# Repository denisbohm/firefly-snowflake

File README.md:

# firefly-snowflake
Firefly Design LLC - Snowflake Christmas Ornament

The snowflake is a Christmas tree ornament with RGB LEDs that light up in various ways.  It has a rechargeable battery (via micro USB port) and it is controllable via BLE via a Swift app.

This repository has all the files to create a snowflake Christmas ornament.  This includes 3D mechanical files to create the plastic parts, Eagle schematics & layout for the PCBA, PCBA firmware, and Swift App source files.

To compile the firmware you need the Nordic nRF5 SDK 12 and Firefly Ice Firmware.  On macOS:

    $ git clone https://github.com/denisbohm/firefly-snowflake.git
    $ cd firefly-snowflake/firmware
    $ git clone https://github.com/denisbohm/firefly-ice-firmware.git
    $ curl https://www.nordicsemi.com/eng/nordic/download_resource/54291/51/54256290 -o nRF5_SDK_12.zip
    $ unzip nRF5_SDK_12.zip -d nRF5_SDK_12

See [Firefly Design LLC](http://fireflydesign.com) for information on the open source Firefly Design repositories.

## Copyright and License
Copyright 2016 Firefly Design LLC / Denis Bohm

This work is licensed under [Creative Commons Attribution 4.0 International](https://licensebuttons.net/l/by/4.0/88x31.png).

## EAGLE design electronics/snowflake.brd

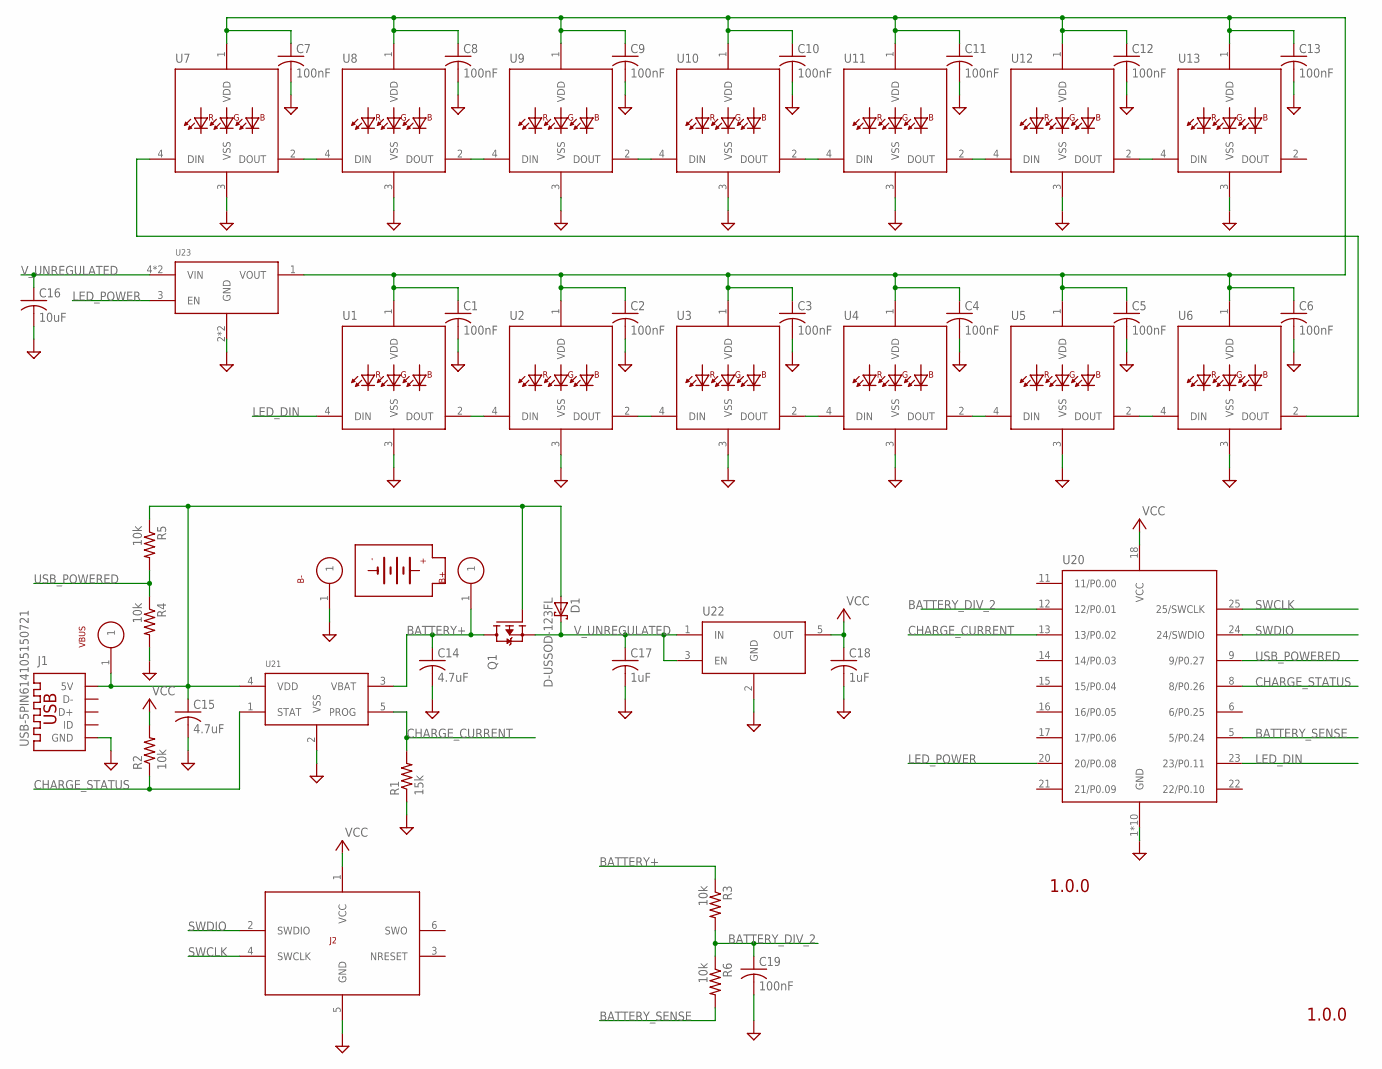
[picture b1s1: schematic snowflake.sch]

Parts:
B1: BATTERY_SHAPEDTP401525; DTP401525
B+: TARGET-PINWP-28AWG; WP-28AWG
B-: TARGET-PINWP-28AWG; WP-28AWG
C1, C2, C3, C4, C5, C6, C7, C8, C9, C10, C11, C12, C13, C19: 100nF; C0805
C14, C15: 4.7uF; C0805
C16: 10uF; C0805
C17, C18: 1uF; C0805
D1: D-USSOD-123FL; SOD-123FL
J1: USB-5PIN614105150721; 614105150721
J2: TC2030-SWD; TC2030-MCP-NL
Q1: FET-PSOT-23-3; SOT-23-3
R1: 15k; R0805
R2, R3, R4, R5, R6: 10k; R0805
U1, U2, U3, U4, U5, U6, U7, U8, U9, U10, U11, U12, U13: WS2812B
U20: BMD-200
U21: MCP73832SOT-23-5; SOT-23-5
U22: ADP160; TSOT-5
U23: TPS22929D; SOT-23-6
VBUS: TARGET-PIN; TARGET-PIN-1MM

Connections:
BATTERY+: B+.1, C14.1, Q1.3 (D), R3.1, U21.3 (VBAT)
BATTERY_DIV_2: C19.1, R3.2, R6.1, U20.12 (12/P0.01)
BATTERY_SENSE: R6.2, U20.5 (5/P0.24)
CHARGE_CURRENT: R1.2, U20.13 (13/P0.02), U21.5 (PROG)
CHARGE_STATUS: R2.1, U20.8 (8/P0.26), U21.1 (STAT)
GND: B-.1, C1.2, C2.2, C3.2, C4.2, C5.2, C6.2, C7.2, C8.2, C9.2, C10.2, C11.2, C12.2, C13.2, C14.2, C15.2, C16.2, C17.2, C18.2, C19.2, J1.5 (GND), J2.5 (GND), R1.1, R4.2, U1.3 (VSS), U2.3 (VSS), U3.3 (VSS), U4.3 (VSS), U5.3 (VSS), U6.3 (VSS), U7.3 (VSS), U8.3 (VSS), U9.3 (VSS), U10.3 (VSS), U11.3 (VSS), U12.3 (VSS), U13.3 (VSS), U20.1 (GND), U20.2 (GND), U20.3 (GND), U20.4 (GND), U20.7 (GND), U20.10 (GND), U20.19 (GND), U20.26 (GND), U20.27 (GND), U20.28 (GND), U21.2 (VSS), U22.2 (GND), U23.2 (GND), U23.5 (GND)
LED_DIN: U1.4 (DIN), U20.23 (23/P0.11)
LED_POWER: U20.20 (20/P0.08), U23.3 (EN)
unnamed: U8.2 (DOUT), U9.4 (DIN)
unnamed: U10.2 (DOUT), U11.4 (DIN)
unnamed: U12.2 (DOUT), U13.4 (DIN)
unnamed: U1.2 (DOUT), U2.4 (DIN)
unnamed: U3.2 (DOUT), U4.4 (DIN)
unnamed: U5.2 (DOUT), U6.4 (DIN)
unnamed: U7.2 (DOUT), U8.4 (DIN)
unnamed: U9.2 (DOUT), U10.4 (DIN)
unnamed: U11.2 (DOUT), U12.4 (DIN)
unnamed: U6.2 (DOUT), U7.4 (DIN)
unnamed: U2.2 (DOUT), U3.4 (DIN)
unnamed: U4.2 (DOUT), U5.4 (DIN)
unnamed: C15.1, D1.A, J1.1 (5V), Q1.1 (G), R5.1, U21.4 (VDD), VBUS.1
SWCLK: J2.4 (SWCLK), U20.25 (25/SWCLK)
SWDIO: J2.2 (SWDIO), U20.24 (24/SWDIO)
USB_POWERED: R4.1, R5.2, U20.9 (9/P0.27)
VCC: C18.1, J2.1 (VCC), R2.2, U20.18 (VCC), U22.5 (OUT)
VCC1: C1.1, C2.1, C3.1, C4.1, C5.1, C6.1, C7.1, C8.1, C9.1, C10.1, C11.1, C12.1, C13.1, U1.1 (VDD), U2.1 (VDD), U3.1 (VDD), U4.1 (VDD), U5.1 (VDD), U6.1 (VDD), U7.1 (VDD), U8.1 (VDD), U9.1 (VDD), U10.1 (VDD), U11.1 (VDD), U12.1 (VDD), U13.1 (VDD), U23.1 (VOUT)
V_UNREGULATED: C16.1, C17.1, D1.C, Q1.2 (S), U22.1 (IN), U22.3 (EN), U23.4 (VIN), U23.6 (VIN)

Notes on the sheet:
1.0.0

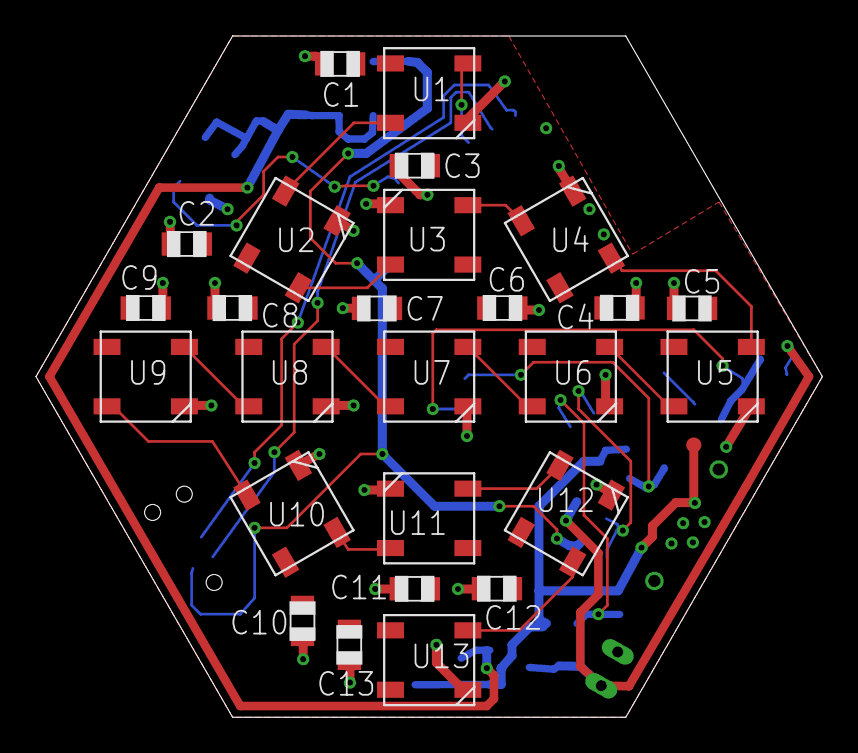
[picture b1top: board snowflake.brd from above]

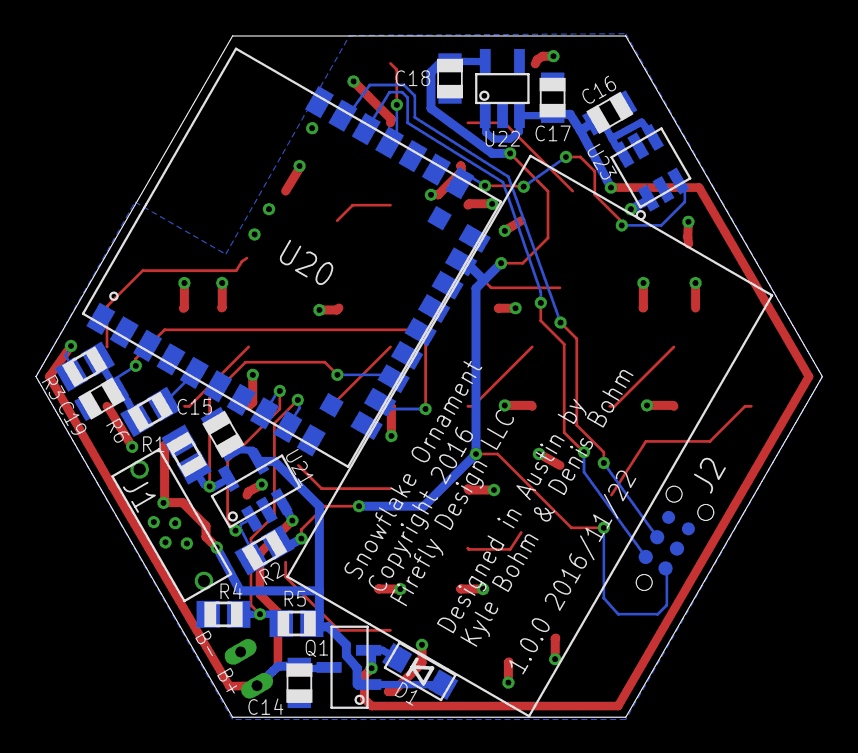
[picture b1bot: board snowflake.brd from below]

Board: 2 copper layers, 43.7 x 37.8 mm, 50 parts (23 on the bottom side), 27 nets.

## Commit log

2016-11-21 add license to readme
2016-11-21 added revision number to schematic and layout
2016-11-21 add project description
2016-11-22 update silk
2016-12-08 communication to LED controller working
2016-12-09 add simulator for trying out lighting patterns quickly on the mac
2016-12-10 BLE initialized correctly
2016-12-12 add breathe animation to firmware
2016-12-17 timeslots working
2016-12-24 25uA with LEDs off
2017-06-28 new animation
2020-11-26 misc tweaks
2020-12-14 simulator update; new led animation option

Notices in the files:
parts and their libraries:
firefly: ©2009 ROFA.cz
